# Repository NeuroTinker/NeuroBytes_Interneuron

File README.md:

# NeuroBytes Interneuron

The Interneuron is an open-source hardware neuron simulator designed and sold by [NeuroTinker, LLC](http://www.neurotinker.com/). Each device includes a number of inputs (dendrites) and outputs (the axon terminal) that can be freely connected to other NeuroBytes boards using 4-pin 'neurotransmitter' cables. Interneurons use a single RGB LED to indicate current status, and include a side-mounted push button for network identification. 

All NeuroBytes products are based on the ST32L0x series of ARM Cortex-M0+ 32-bit microcontrollers. The boards were designed in KiCad and Inkscape and are released under the terms of the Creative Commons Attribution-ShareAlike 4.0 license, available here: http://creativecommons.org/licenses/by-sa/4.0/. The NeuroBytes Interneuron is Certified Open Source Hardware as defined by [OSHWA](https://www.oshwa.org), certification number US000113.

This repository is a continuation of the 8-bit ATtiny design called [NeuroBytes v0.91](https://github.com/zakqwy/neurobytes). The two series are not compatible.

## Project Status
This project is in alpha. The firmware is in progress and the API may change at any time. The PCB design is physically tested but has not yet been manufactured at scale.

## More Information
The NeuroBytes GitHub repositories store engineering information and make the design history of the project available to the public. Hardware- and firmware-specific README.md files can be found in their appropriate subdirectories. 

We encourage community involvement in our efforts, keeping in mind that hardware availability is currently quite limited. For product availability, operating guidelines, curricula, and information about NeuroTinker, LLC, head to neurotinker.com. Further technical logs are also at https://hackaday.io/project/3339-neurobytes.

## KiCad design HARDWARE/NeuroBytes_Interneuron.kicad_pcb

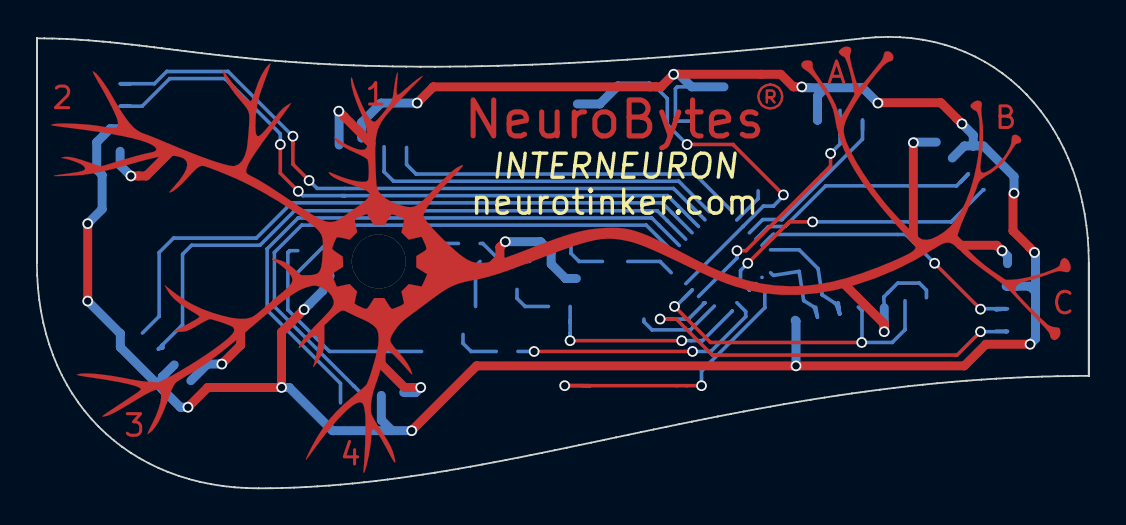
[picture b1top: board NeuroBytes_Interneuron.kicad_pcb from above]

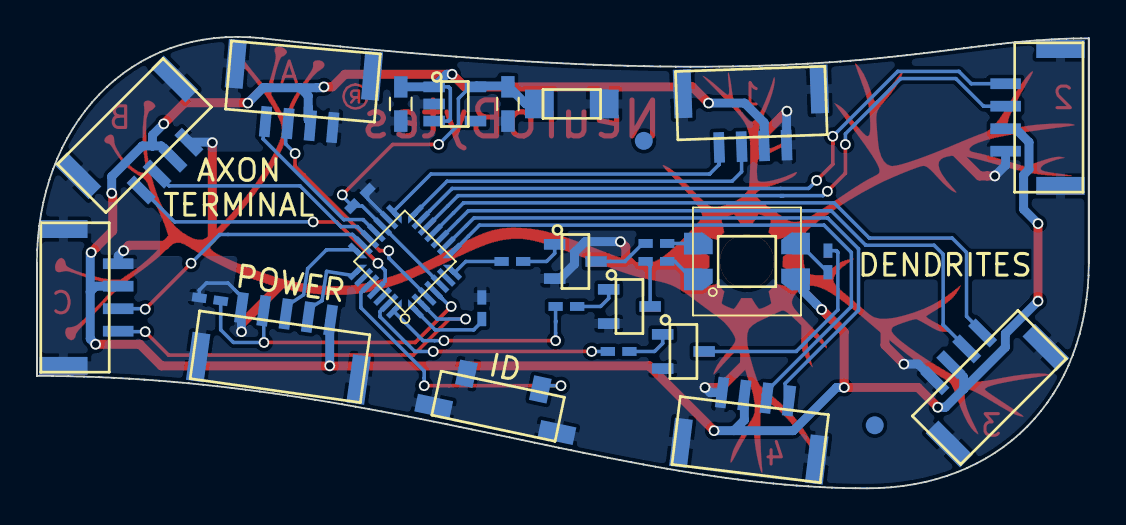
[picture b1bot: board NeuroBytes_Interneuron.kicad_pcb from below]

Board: 2 copper layers, 58.4 x 25.1 mm, 27 parts (27 on the bottom side), 34 nets.

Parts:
C1, C4: 1u0; C_0603_HandSoldering
C2: 10u; ZF_SMD_nonpol_1206
C3, C5: 0u1; ZF_SMD_NonPol_0402_cap
D1: LED_RABG; ZF_LED_RGB_SunLED_XZMDKCBDDG45S-9_cast
P1, P2, P3, P4, P5, P6, P7: JST GH 4-POS; ZF_CONN_JST_GH
P8: JST_GH_5-pos; ZF_CONN_JST_GH_5POS
Q1, Q2, Q3: MMBT3904; ZF_SOT23-3L
R1: 150; ZF_SMD_NonPol_0402
R2, R3: 100; ZF_SMD_NonPol_0402
R4: JMP; ZF_SMD_NonPol_0402
R5, R6, R7: 1k; ZF_SMD_NonPol_0402
SW1: SW_PUSH_TL3330AF130QG; ZF_SW_Momentary_SideMtg
U1: STM32L011Gx; ZF_IC_UFQFPN28-050
U2: TLV702; ZF_SOT23-5L

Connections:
+3V3: C2.1, C3.1, C4.1, U1.5, U1.17, U2.5
+5V: C1.1, D1.2, P1.2, P2.2, P3.2, P4.2, P5.2, P6.2, P7.2, P8.5, U2.1, U2.3
A1EX: P6.4, U1.18
A1IN: P6.3, U1.3
A2EX: P7.4, U1.25
A2IN: P7.3, U1.19
A3EX: P5.4, U1.2
A3IN: P5.3, U1.20
D1EX: P1.4, U1.15
D1IN: P1.3, U1.14
D2EX: P2.4, U1.13
D2IN: P2.3, U1.12
D3EX: P3.4, U1.11
D3IN: P3.3, U1.10
D4EX: P4.4, U1.9
D4IN: P4.3, U1.8
GND: C1.2, C2.2, C3.2, C4.2, C5.2, P1.1, P2.1, P3.1, P4.1, P5.1, P6.1, P7.1, P8.1, Q1.2, Q2.2, Q3.2, R4.2, SW1.1, U1.16, U2.2
LED_B: R7.2, U1.27
LED_G: R6.2, U1.7
LED_R: R5.2, U1.28
unnamed: D1.1, R1.1
unnamed: D1.3, R3.1
unnamed: D1.4, R2.1
unnamed: Q1.1, R5.1
unnamed: Q1.3, R1.2
unnamed: Q2.1, R6.1
unnamed: Q2.3, R2.2
unnamed: Q3.1, R7.1
unnamed: Q3.3, R3.2
unnamed: R4.1, U1.1
RESET: C5.1, P8.2, U1.4
SWCLK: P8.4, U1.22
SWDIO: P8.3, U1.21
SWITCH: SW1.2, U1.24

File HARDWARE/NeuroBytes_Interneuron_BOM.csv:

Title,NeuroBytes Interneuron,,,,,,,
Revision,C,,,,,,,
Date,2017-05-15,,,,,,,
Generated,Mon 15 May 2017 08:22:36 PM CDT,,,,,,,
Company,NeuroTinker, LLC,,,,,,
Comment 1,,,,,,,,
Comment 2,,,,,,,,
Comment 3,,,,,,,,
Comment 4,,,,,,,,
Total Parts,24,,,,,,,
Total Unique Parts,14,,,,,,,
,,,,,,,,
,,,,,,,,
,,,,,,,,
Ref,Qty,Value,Link,Mfr,Mfr Part #,Package,RoHS,Subs Allowed
C3 C5,2,100 nF,https://www.digikey.com/product-detail/en/taiyo-yuden/LMK105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,Taiyo Yuden,LMK105BJ104KV-F,0402,Yes,No
C1 C4 ,2,1 uF,https://www.digikey.com/product-detail/en/taiyo-yuden/LMK107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,Taiyo Yuden,LMK107B7105KA-T,0603,Yes,Yes
C2 ,1,10 uF,https://www.digikey.com/product-detail/en/kemet/T491A106K010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,Kemet,T491A106K010AT,1206,Yes,No
D1 ,1,RGB LED CA,https://www.digikey.com/product-detail/en/sunled/XZMDKCBDDG4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,SunLED,XZMDKCBDDG45S-9,4-PLCC  bottom mtg,Yes,No
P1 P6 P7 P2 P3 P4 P5 ,7,JST GH 4-POS,N/A (NeuroTinker supplied),JST,SM04B-GHS-GD-TB(LF)(SN),SMT,Yes,No
P8,1,JST GH 7-POS,https://www.digikey.com/product-detail/en/jst-sales-america-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,JST,SM07B-GHS-TB(LF)(SN),SMT,Yes,No
Q2 Q1 ,2,NPN 3904 Dual,https://www.digikey.com/product-detail/en/on-semiconductor/M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,ON Semiconductor,MBT3904DW1T1G,SOT-363,Yes,Yes
R1 ,1,150,https://www.digikey.com/product-detail/en/yageo/RC0402FR-071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,Yageo,RC0402FR-07150RL,0402,Yes,Yes
R2 R3 ,2,100,https://www.digikey.com/product-detail/en/yageo/RC0402FR-071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,Yageo,RC0402FR-07100RP,0402,Yes,Yes
R4 ,1,Jumper (0 ohm),https://www.digikey.com/product-detail/en/yageo/RC0402JR-070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,Yageo,RC0402JR-070RL,0402,Yes,Yes
RN1 ,1,1k (x4),https://www.digikey.com/product-detail/en/cts-resistor-produ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,CTS Resistor Products,741C083103JP,0804,Yes,Yes
SW1 ,1,SW_PUSH_TL3330AF130QG,https://www.digikey.com/product-detail/en/e-switch/TL3330AF1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,E-Switch,TL3330AF130QG,Gull Wing,Yes,No
U1 ,1,STM32L011Gx,N/A (NeuroTinker supplied),ST Microelectronics,STM32L011G4U6,28-UFQFN,Yes,No
U2 ,1,LDO_LD3985M33R,https://www.digikey.com/product-detail/en/stmicroelectronics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,ST Microelectronics,LD3985M33R,SOT-23-5,Yes,No
,,,,,,,,
,,,,,,,,
,,,,,,,,
,,,,,,,,
BOM made with KICAD_BOM_WIZARD (https://github.com/HashDefineElectronics/KiCad_BOM_Wizard.git),,,,,,,,
Generated Mon 15 May 2017 08:22:36 PM CDT,,,,,,,,

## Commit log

2017-03-16 Initial commit. Implemented libopencm3 as a git submodule following instructions from libopencm3-examples. Note that stm32l0xx4.ld was added to /libopencm3/lib/stm32/l0 (still in testing). Actual Neu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
2017-03-17 Got rid of helloworld test program and replaced with a basic hardware abstraction library and main code. Configurable for LED PWM testing on both the Motor Neuron and NeuroBytes v1.01 PCB designs (wh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
2017-03-31 Add files via upload
    First commit with communication protocol
2017-05-09 Initial hardware design files upload.
2017-05-12 finished porting v0.91 functionality
2017-05-12 fixed dropped packet issue
2017-05-15 added schematic library submodule
2017-05-15 Updated project file to include schematic library submodule
2017-05-16 Added PCB mfr notes on FAB layer. Modified QFN28 footprint to comply with IPC-7351FC Level B.
2017-05-16 Generated Gerber files, drill file, BOM, and placement file. Changed 7-pin JST connector designator to P8 (was P12, and P9-P11 don't exist).
2017-05-16 Cleaned up old Gerber files (that weren't in the HARDWARE/gerbers directory). Minor PCB updates.
2017-05-16 Added license to schematic and layout title blocks. Updated BOM file name.
2017-05-16 Updated Gerbers directory because 'Gerbers' should be capitalized. Thanks, Joseph Gerber.
2017-05-19 make clean
2017-05-19 Added Interneuron picture
2017-05-19 Removed image. Going to make a page on GitHub.
2017-05-19 Set theme jekyll-theme-minimal
2017-05-19 updating pyserial submodule so pages can work
2017-05-24 Removed scripts
2017-05-24 commented and cleaned up
2017-05-24 All warnings resolved
2017-05-25 changed libopencm3 url
2017-05-26 revised comments
2017-05-26 more commenting
2017-05-26 updated comments
2017-05-26 added leaky current
2017-05-26 changed .gitignore
2017-05-31 Updated switch footprint (centered, removed part of support pad). Updated JST footprints (centered). BOM changes to reduce mfr cost: dual --> single NPN transistors; resistor network --> discrete res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
2017-06-14 getting ready for merge
2017-06-14 added bit-bang
2017-06-21 reorganized filesystem for tests
2017-06-23 updated tests
2017-06-27 rewriting HAL
2017-06-27 release
2017-06-27 fixed memory segmentation bug
2017-06-28 fixed bug
2017-06-28 preparing for merge with dev
2017-06-28 preparing for merge
2017-07-18 added tests
2017-07-20 fixed send_message test
2017-07-25 added device id
2017-07-25 changed .gitignore to allow elf
2017-07-25 clean
2017-07-25 reorganized directories
2017-07-25 reorganized
2017-07-25 added fingerprint
2017-08-08 updated fingerprint
2017-08-08 added main.elf to local repo
2017-08-09 Updated PCB outline to eliminate rotational symmetry. Changed to 5-pin JST GH connector for power. Numerous routing changes and minor graphics updates.
2017-08-10 added fingerprint elf offset
2017-08-10 fixed submodules
2017-08-11 changed fingerprint
2017-08-28 updated graphics to include kicad fonts. added png export of board front render.
2017-08-31 moved transistors around a bit so they don't overlap anymore.
2017-08-31 changed gitignore
2017-08-31 added vscode files to .gitignore
2017-08-31 added .json to .gitignore
2017-08-31 new dev branc
2017-08-31 changed comm interrupt to systick
2017-08-31 changed comms interrupt to systick
2017-09-05 simplified illustrations
2017-09-05 illustration update
2017-09-06 illustration updates
2017-09-06 fresh *.png exports
2017-09-06 cleaned up
2017-09-06 added picture to readme.md
2017-09-07 added learning
2017-09-07 emergency cleanup
2017-09-07 added elf
2017-09-07 change bin. roll back this commit
2017-09-08 testing axon delays
2017-09-11 fixed simultaneous excitation issue
2017-09-11 testing antialiasing
2017-09-13 magenta learning mode
2017-09-13 added magenta learning
2017-09-13 added magenta
2017-09-18 added membrane potential inidcation to learning
2017-09-18 recalculated gamma correction table and changed ledFullWhite to reduce resting and A.P. brightness
2017-09-18 testing semihosting with newlib-nano
2017-09-21 enforced .gitignore
2017-09-21 removed newlib nano testing stuff before merge
2017-09-21 updated Gerber fab layer notes. Mostly doing this to test slack integration.
2017-09-21 updated BOM. removed old Gerber files. changed PCB art to use updated gear. pulled back mask on dendrite/axon labels. other minor changes.
2017-09-21 minor BOM updates
2017-09-21 removed merge expressions preventing 'make'
2017-09-22 removed merge decorations
2017-09-22 made fresh elf
2017-09-22 removed src/main.elf
2017-09-22 ran make to update elf files
2017-09-22 minor updates to PCB. updated netlist.
2017-09-26 made elf
2017-10-03 new comms protocol
2017-10-03 nid ping working
2017-10-03 fixed blink bug
2017-10-03 minor title block and page layout changes
2017-10-06 increased white flash duration
2017-10-06 updated LED brightness
2017-10-13 testing lpuart
2017-10-13 debug comments
2017-10-13 usart2 test
2017-10-27 high data rate
2017-11-01 demo build
2017-11-02 cleaned up HAL and comm
2017-11-02 fixed 5-min bug
2017-11-02 fixed axon 1 issue
2017-11-07 added clear nid channel
2017-11-07 removed extraneous comments
2017-11-07 fixed readNID
2017-11-07 fixed warnings
2017-11-07 support for multiple channels
2017-11-08 trying to make common comms and neuron files
2017-11-08 comm and neuron abstraction. fixed write time
2017-11-08 fixed data bug
2017-11-09 dumb hack
2017-11-21 reorganizing for neurobytes common
2017-11-21 building with common
2017-11-21 added neurobytes common
2017-11-21 no more elf in src
2017-11-21 moved fingerprint to HAL for... reasons...
2017-11-21 fixed checkVersion error
2017-11-21 debugging weird LED issue
2017-11-21 reenabled TIM2 isr. wierd fix.
2017-11-21 works with NID
2017-11-27 removed depression
2017-11-27 fixed naming
2017-11-28 support NID-less IDing
2017-11-29 initialize dendritic weightings
2017-11-29 added command parameters
2017-11-29 fixed init error
2017-11-29 fix bug where data transmits after NID disconnect
2017-11-29 updated license and readme to CC-BY-SA 4.0. added drawing number to PCB layout.
2017-11-30 id fix
2018-01-25 small improvements. build elf
2018-01-30 merging main
2018-01-31 fixed DBG issue
2018-01-31 DBG disabled
2018-01-31 temp debug
2018-02-01 changed dendrite weightings
2018-02-06 implemented pause/resume
2018-02-13 added ESD protection. updated title block.
2018-03-08 increased long dendrite weightings
2018-03-08 minor PCB render updates
2018-03-08 added OSHWA cert logo to README.md
2018-03-09 added nid parameter cmds
2018-04-03 emc build
2018-04-10 made elf. (arizona build)
2018-05-10 fixed learning
2018-05-10 experimental learning indication
2018-05-10 added 10 sec depression delay. old indication
2018-05-18 Joe's changes
2018-05-23 message fix
2018-05-23 mem indication test
2018-05-23 removed ESD protection (not needed during testing). generated fab files and BOM.
2018-05-23 updated INSERT attribute. regenerated *.pos file.
2018-05-24 support for new messages
2018-05-24 fixed type message
2018-05-31 added schematic *.pdf
2018-06-18 added specific commands
2018-06-19 more command support
2018-08-08 updated footprints to include B.Fab outlines. minor routing changes. re-generated Gerbers. added placement pdf.
2018-08-08 regen drill file
2018-12-28 testing elf
2018-12-29 increased LED brightness

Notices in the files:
HARDWARE/NeuroBytes_Interneuron.kicad_pcb:
(C) 2017 Zach Fredin
License: CC-BY-SA 4.0
